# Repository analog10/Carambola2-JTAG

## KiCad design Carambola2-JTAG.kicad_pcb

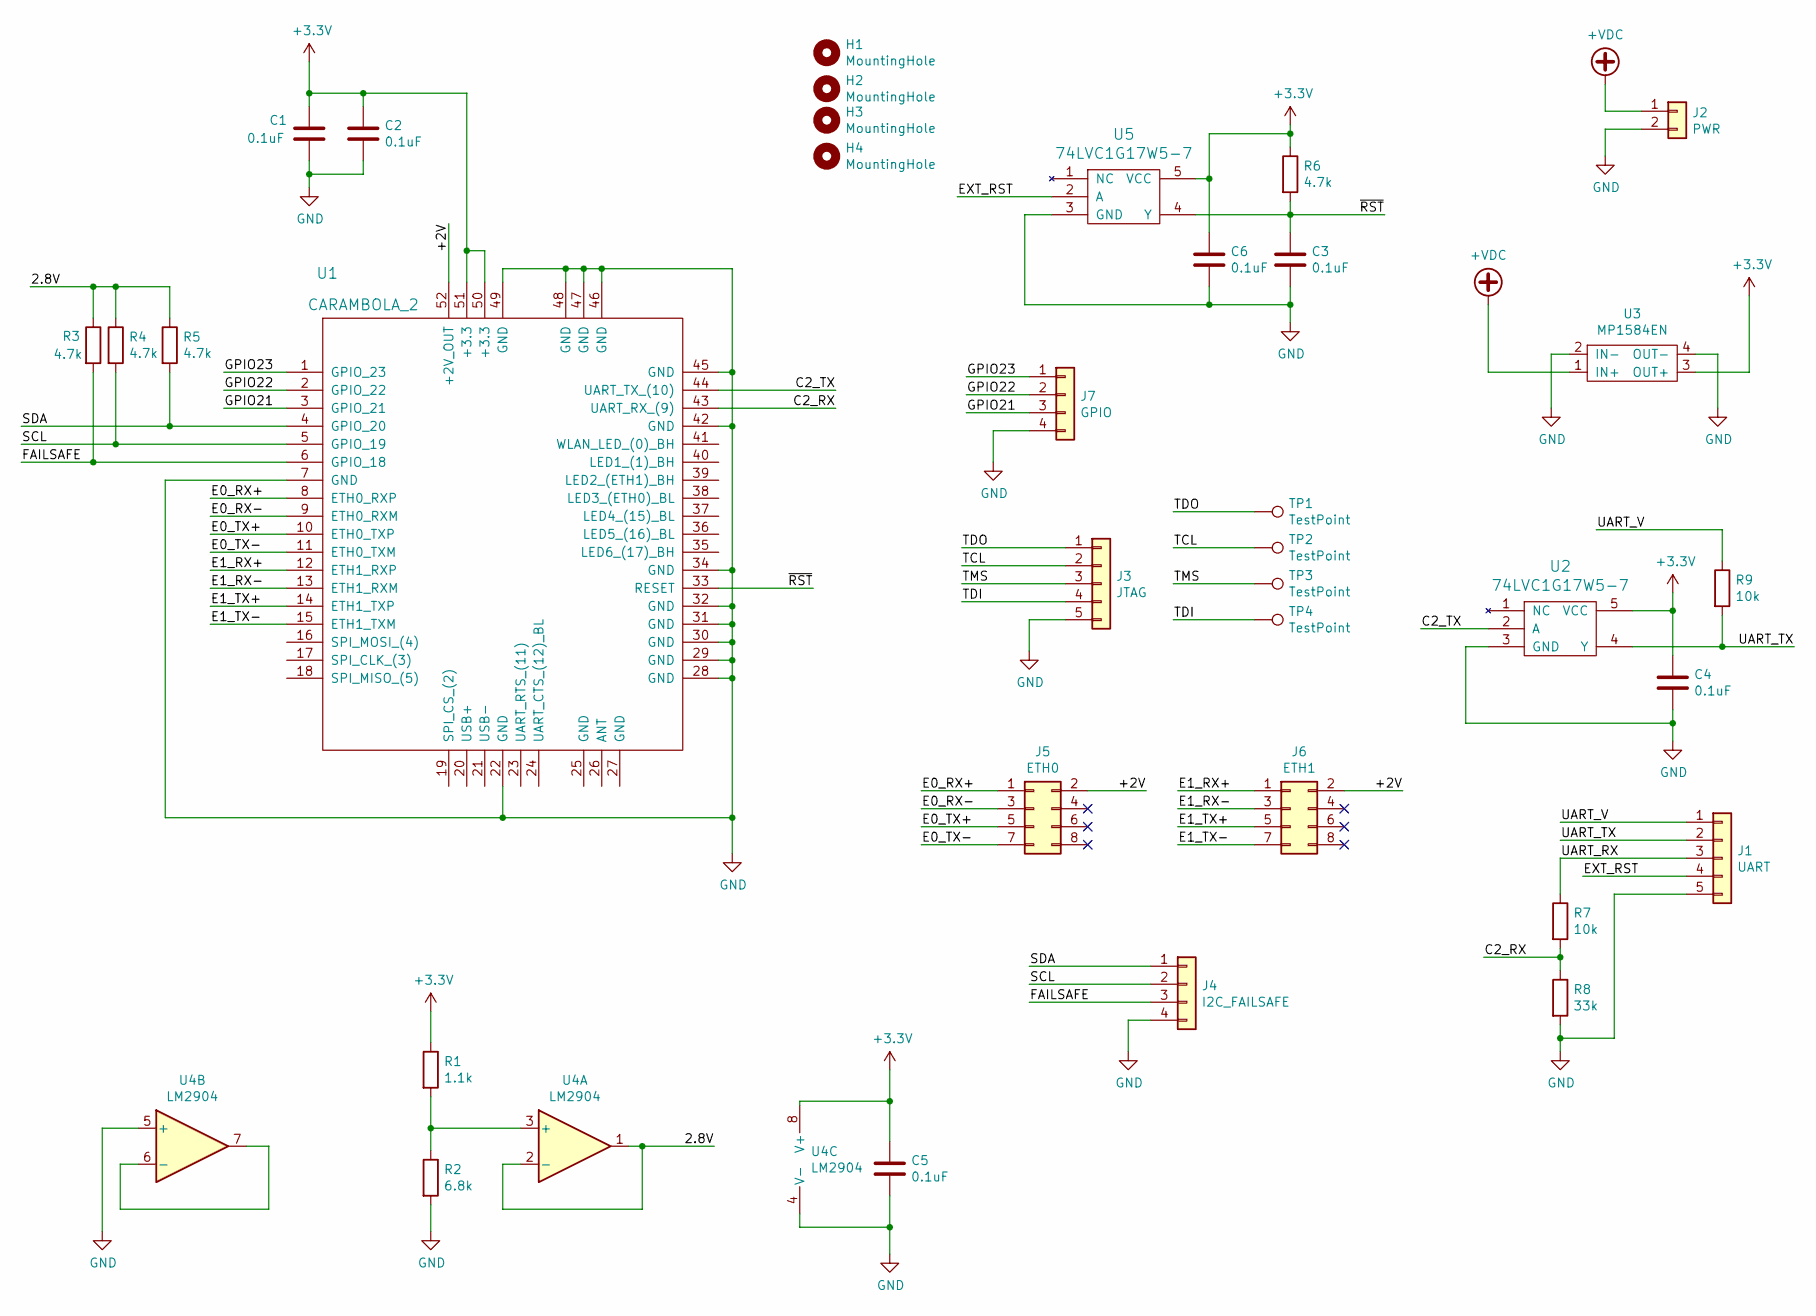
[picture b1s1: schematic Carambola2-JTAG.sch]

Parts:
C1, C2, C3, C4, C5, C6: 0.1uF; C_Disc_D4.3mm_W1.9mm_P5.00mm
H1, H2, H3, H4: MountingHole; MountingHole_3.2mm_M3
J1: UART; PinHeader_1x05_P2.54mm_Vertical
J2: PWR; PinHeader_1x02_P2.54mm_Vertical
J3: JTAG; PinHeader_1x05_P2.54mm_Vertical
J4: I2C_FAILSAFE; PinHeader_2x02_P2.00mm_Vertical
J5: ETH0; PinHeader_2x04_P2.00mm_Vertical
J6: ETH1; PinHeader_2x04_P2.00mm_Vertical
J7: GPIO; PinHeader_1x04_P2.00mm_Vertical
R1: 1.1k; R_Axial_DIN0204_L3.6mm_D1.6mm_P5.08mm_Horizontal
R2: 6.8k; R_Axial_DIN0204_L3.6mm_D1.6mm_P5.08mm_Horizontal
R3, R4, R5, R6: 4.7k; R_Axial_DIN0204_L3.6mm_D1.6mm_P5.08mm_Horizontal
R7, R9: 10k; R_Axial_DIN0204_L3.6mm_D1.6mm_P5.08mm_Horizontal
R8: 33k; R_Axial_DIN0204_L3.6mm_D1.6mm_P5.08mm_Horizontal
TP1, TP2, TP3, TP4: TestPoint; TestPoint_Pad_D2.5mm
U1: CARAMBOLA_2
U2, U5: 74LVC1G17W5-7; SOT-23-5_HandSoldering
U3: MP1584EN
U4: LM2904; DIP-8_W7.62mm

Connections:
+3V3: C1.1, C2.1, C4.1, C5.1, C6.1, R1.1, R6.1, U1.50 (+3.3), U1.51 (+3.3), U2.5 (VCC), U3.3 (OUT+), U4.8 (V+), U5.5 (VCC)
+VDC: J2.1, U3.1 (IN+)
/2.8V: R3.1, R4.1, R5.1, U4.1, U4.2 (-)
/+2V: J5.2, J6.2, U1.52 (+2V_OUT)
/C2_RX: R7.2, R8.1, U1.43 (UART_RX_(9))
/C2_TX: U1.44 (UART_TX_(10)), U2.2 (A)
/E0_RX+: J5.1, U1.8 (ETH0_RXP)
/E0_RX-: J5.3, U1.9 (ETH0_RXM)
/E0_TX+: J5.5, U1.10 (ETH0_TXP)
/E0_TX-: J5.7, U1.11 (ETH0_TXM)
/E1_RX+: J6.1, U1.12 (ETH1_RXP)
/E1_RX-: J6.3, U1.13 (ETH1_RXM)
/E1_TX+: J6.5, U1.14 (ETH1_TXP)
/E1_TX-: J6.7, U1.15 (ETH1_TXM)
/EXT_RST: J1.4, U5.2 (A)
/FAILSAFE: J4.3, R3.2, U1.6 (GPIO_18)
/GPIO21: J7.3, U1.3 (GPIO_21)
/GPIO22: J7.2, U1.2 (GPIO_22)
/GPIO23: J7.1, U1.1 (GPIO_23)
/SCL: J4.2, R4.2, U1.5 (GPIO_19)
/SDA: J4.1, R5.2, U1.4 (GPIO_20)
/TCL: J3.2, TP2.1
/TDI: J3.4, TP4.1
/TDO: J3.1, TP1.1
/TMS: J3.3, TP3.1
/UART_RX: J1.3, R7.1
/UART_TX: J1.2, R9.2, U2.4 (Y)
/UART_V: J1.1, R9.1
/~RST: C3.1, R6.2, U1.33 (RESET), U5.4 (Y)
GND: C1.2, C2.2, C3.2, C4.2, C5.2, C6.2, J1.5, J2.2, J3.5, J4.4, J7.4, R2.2, R8.2, U1.7 (GND), U1.22 (GND), U1.28 (GND), U1.29 (GND), U1.30 (GND), U1.31 (GND), U1.32 (GND), U1.34 (GND), U1.42 (GND), U1.45 (GND), U1.46 (GND), U1.47 (GND), U1.48 (GND), U1.49 (GND), U2.3 (GND), U3.2 (IN-), U3.4 (OUT-), U4.4 (V-), U4.5 (+), U5.3 (GND)
unnamed: R1.2, R2.1, U4.3 (+)
unnamed: U4.6 (-), U4.7

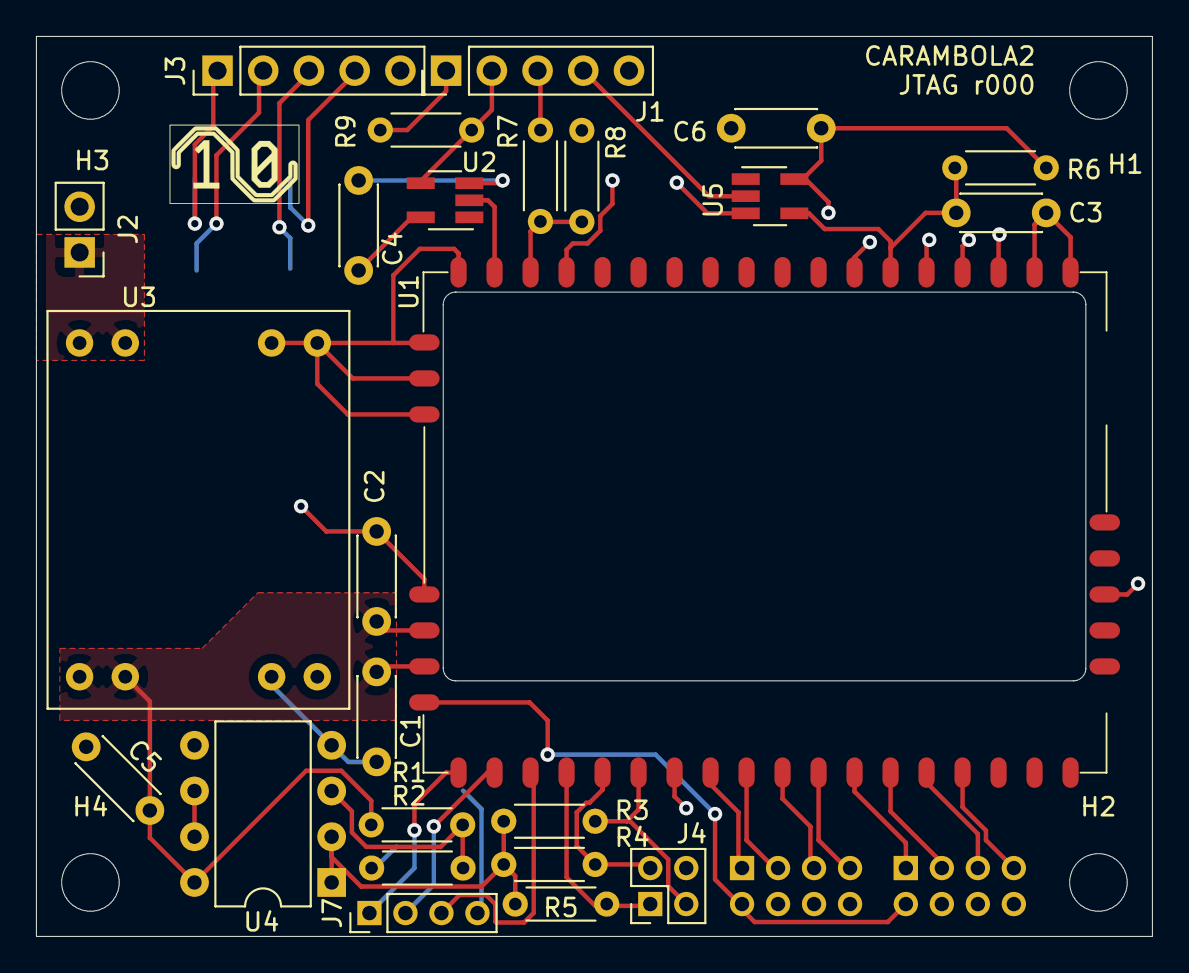
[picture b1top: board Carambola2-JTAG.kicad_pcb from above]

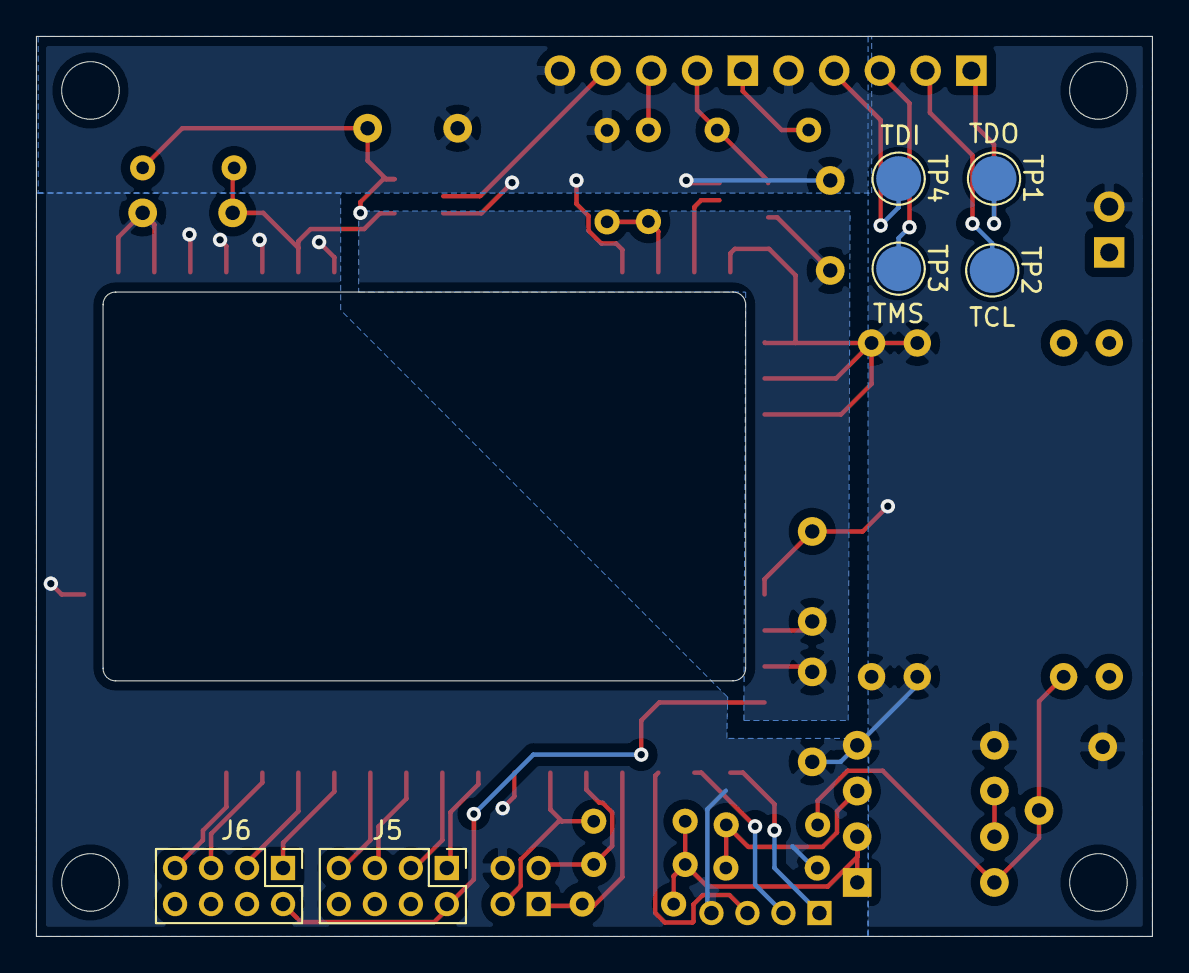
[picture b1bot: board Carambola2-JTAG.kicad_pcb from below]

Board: 2 copper layers, 62.0 x 50.0 mm, 35 parts (6 on the bottom side), 32 nets.

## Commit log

2022-07-20 Add files via upload
    initial commit
